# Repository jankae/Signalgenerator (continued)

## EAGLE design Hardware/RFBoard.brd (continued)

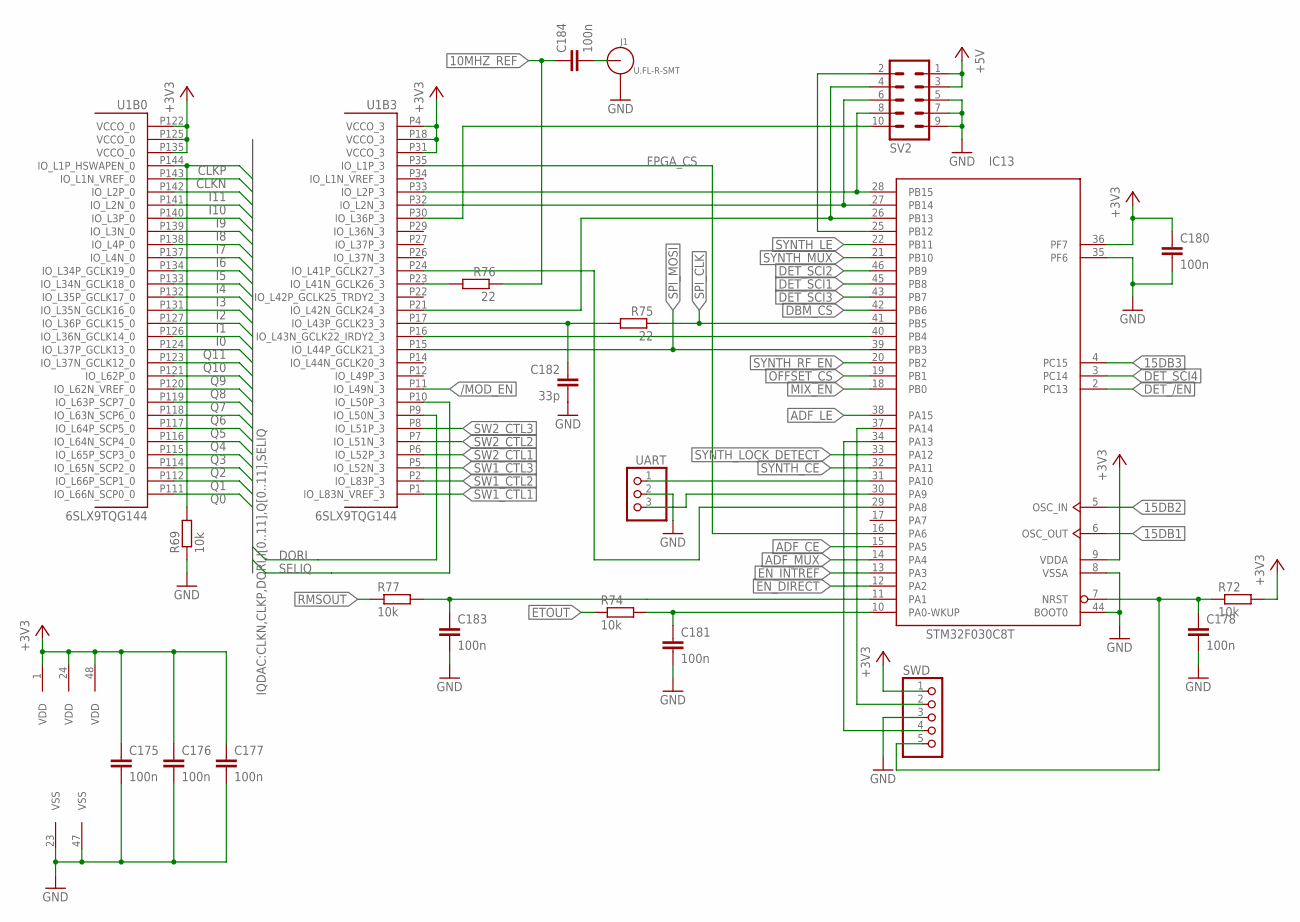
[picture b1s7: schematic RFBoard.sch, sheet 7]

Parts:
C175, C176, C177, C178, C180, C181, C183, C184: 100n; C0603
C182: 33p; C0603
IC13: STM32F030C8T; LQFP48
J1: U.FL-R-SMT; U.FL_SMT
R69, R72, R74, R77: 10k; R0603
R75, R76: 22; R0603
SV2: ML10
SWD: PINHD-1X5; 1X05
U1: 6SLX9TQG144; TQ144
UART: PINHD-1X3; 1X03

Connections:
10MHZ_REF: C184.1, R76.1; also elsewhere on the board
15DB1: IC13.6 (OSC_OUT); also elsewhere on the board
15DB2: IC13.5 (OSC_IN); also elsewhere on the board
15DB3: IC13.4 (PC15); also elsewhere on the board
+3V3: C175.1, C176.1, C177.1, C180.1, IC13.1 (VDD), IC13.9 (VDDA), IC13.24 (VDD), IC13.36 (PF7), IC13.48 (VDD), R72.2, SWD.1, U1.P4 (VCCO_3), U1.P18 (VCCO_3), U1.P31 (VCCO_3), U1.P122 (VCCO_0), U1.P125 (VCCO_0), U1.P135 (VCCO_0); also elsewhere on the board
+5V: SV2.1, SV2.3; also elsewhere on the board
/MOD_EN: U1.P11 (IO_L49N_3); also elsewhere on the board
ADF_CE: IC13.15 (PA5); also elsewhere on the board
ADF_LE: IC13.38 (PA15); also elsewhere on the board
ADF_MUX: IC13.14 (PA4); also elsewhere on the board
CLKN: U1.P143 (IO_L1N_VREF_0); also elsewhere on the board
CLKP: R69.2, U1.P144 (IO_L1P_HSWAPEN_0); also elsewhere on the board
CS: IC13.25 (PB12), SV2.2
CS_FPGA: SV2.10, U1.P30 (IO_L36P_3)
DBM_CS: IC13.42 (PB6); also elsewhere on the board
DET_/EN: IC13.2 (PC13); also elsewhere on the board
DET_SCI1: IC13.45 (PB8); also elsewhere on the board
DET_SCI2: IC13.46 (PB9); also elsewhere on the board
DET_SCI3: IC13.43 (PB7); also elsewhere on the board
DET_SCI4: IC13.3 (PC14); also elsewhere on the board
DORI: U1.P9 (IO_L50N_3); also elsewhere on the board
EN_DIRECT: IC13.12 (PA2); also elsewhere on the board
EN_INTREF: IC13.13 (PA3); also elsewhere on the board
ETOUT: R74.1; also elsewhere on the board
FPGA_CS: IC13.16 (PA6), U1.P35 (IO_L1P_3)
GND: C175.2, C176.2, C177.2, C178.2, C180.2, C181.2, C182.2, C183.2, IC13.8 (VSSA), IC13.23 (VSS), IC13.35 (PF6), IC13.44 (BOOT0), IC13.47 (VSS), J1.GND1, J1.GND2, R69.1, SV2.5, SV2.7, SV2.9, SWD.3, UART.2; also elsewhere on the board
I0: U1.P126 (IO_L36N_GCLK14_0); also elsewhere on the board
I1: U1.P127 (IO_L36P_GCLK15_0); also elsewhere on the board
I2: U1.P131 (IO_L35N_GCLK16_0); also elsewhere on the board
I3: U1.P132 (IO_L35P_GCLK17_0); also elsewhere on the board
I4: U1.P133 (IO_L34N_GCLK18_0); also elsewhere on the board
I5: U1.P134 (IO_L34P_GCLK19_0); also elsewhere on the board
I6: U1.P137 (IO_L4N_0); also elsewhere on the board
I7: U1.P138 (IO_L4P_0); also elsewhere on the board
I8: U1.P139 (IO_L3N_0); also elsewhere on the board
I9: U1.P140 (IO_L3P_0); also elsewhere on the board
I10: U1.P141 (IO_L2N_0); also elsewhere on the board
I11: U1.P142 (IO_L2P_0); also elsewhere on the board
MISO: IC13.27 (PB14), SV2.6, U1.P32 (IO_L2N_3)
MIX_EN: IC13.18 (PB0); also elsewhere on the board
MOSI: IC13.28 (PB15), SV2.8, U1.P33 (IO_L2P_3)
unnamed: C183.1, IC13.11 (PA1), R77.2
unnamed: C184.2, J1.SIG (ANT)
unnamed: IC13.29 (PA8), U1.P24 (IO_L41P_GCLK27_3)
unnamed: C181.1, IC13.10 (PA0-WKUP), R74.2
unnamed: C182.1, R75.2, U1.P17 (IO_L43P_GCLK23_3)
unnamed: IC13.40 (PB4), U1.P16 (IO_L43N_GCLK22_IRDY2_3)
unnamed: R76.2, U1.P23 (IO_L41N_GCLK26_3)
NRST: C178.1, IC13.7 (NRST), R72.1, SWD.5
OFFSET_CS: IC13.19 (PB1); also elsewhere on the board
Q0: U1.P111 (IO_L66N_SCP0_0); also elsewhere on the board
Q1: U1.P112 (IO_L66P_SCP1_0); also elsewhere on the board
Q2: U1.P114 (IO_L65N_SCP2_0); also elsewhere on the board
Q3: U1.P115 (IO_L65P_SCP3_0); also elsewhere on the board
Q4: U1.P116 (IO_L64N_SCP4_0); also elsewhere on the board
Q5: U1.P117 (IO_L64P_SCP5_0); also elsewhere on the board
Q6: U1.P118 (IO_L63N_SCP6_0); also elsewhere on the board
Q7: U1.P119 (IO_L63P_SCP7_0); also elsewhere on the board
Q8: U1.P120 (IO_L62N_VREF_0); also elsewhere on the board
Q9: U1.P121 (IO_L62P_0); also elsewhere on the board
Q10: U1.P123 (IO_L37N_GCLK12_0); also elsewhere on the board
Q11: U1.P124 (IO_L37P_GCLK13_0); also elsewhere on the board
RMSOUT: R77.1; also elsewhere on the board
RX: IC13.31 (PA10), UART.1
SCK: IC13.26 (PB13), SV2.4, U1.P21 (IO_L42N_GCLK24_3)
SELIQ: U1.P10 (IO_L50P_3); also elsewhere on the board
SPI_CLK: IC13.41 (PB5), R75.1; also elsewhere on the board
SPI_MOSI: IC13.39 (PB3), U1.P15 (IO_L44P_GCLK21_3); also elsewhere on the board
SW1_CTL1: U1.P1 (IO_L83N_VREF_3); also elsewhere on the board
SW1_CTL2: U1.P2 (IO_L83P_3); also elsewhere on the board
SW1_CTL3: U1.P5 (IO_L52N_3); also elsewhere on the board
SW2_CTL1: U1.P6 (IO_L52P_3); also elsewhere on the board
SW2_CTL2: U1.P7 (IO_L51N_3); also elsewhere on the board
SW2_CTL3: U1.P8 (IO_L51P_3); also elsewhere on the board
SWCLK: IC13.37 (PA14), SWD.2
SWDIO: IC13.34 (PA13), SWD.4
SYNTH_CE: IC13.32 (PA11); also elsewhere on the board
SYNTH_LE: IC13.22 (PB11); also elsewhere on the board
SYNTH_LOCK_DETECT: IC13.33 (PA12); also elsewhere on the board
SYNTH_MUX: IC13.21 (PB10); also elsewhere on the board
SYNTH_RF_EN: IC13.20 (PB2); also elsewhere on the board
TX: IC13.30 (PA9), UART.3

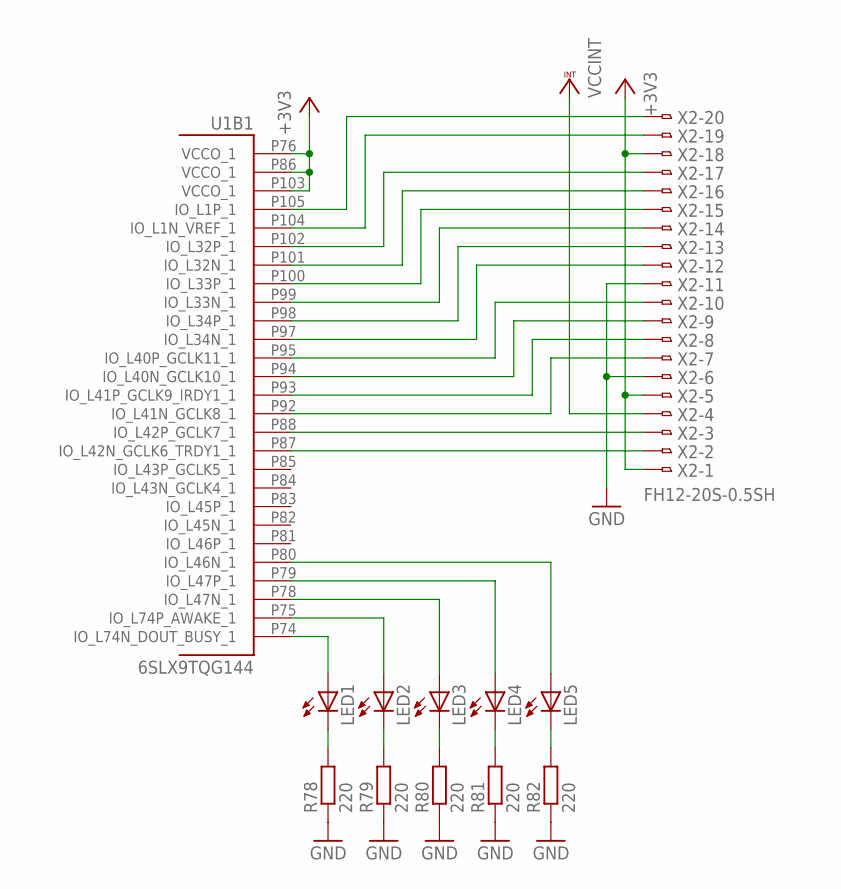
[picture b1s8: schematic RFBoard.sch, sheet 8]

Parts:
LED1, LED2, LED3, LED4, LED5: LEDCHIP-LED0603; CHIP-LED0603
R78, R79, R80, R81, R82: 220; R0603
U1: 6SLX9TQG144; TQ144
X2: FH12-20S-0.5SH

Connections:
+3V3: U1.P76 (VCCO_1), U1.P86 (VCCO_1), U1.P103 (VCCO_1), X2.1, X2.5, X2.18; also elsewhere on the board
GND: R78.1, R79.1, R80.1, R81.1, R82.1, X2.6, X2.11; also elsewhere on the board
unnamed: U1.P100 (IO_L33P_1), X2.15
unnamed: U1.P87 (IO_L42N_GCLK6_TRDY1_1), X2.2
unnamed: U1.P88 (IO_L42P_GCLK7_1), X2.3
unnamed: U1.P92 (IO_L41N_GCLK8_1), X2.7
unnamed: U1.P93 (IO_L41P_GCLK9_IRDY1_1), X2.8
unnamed: U1.P94 (IO_L40N_GCLK10_1), X2.9
unnamed: U1.P95 (IO_L40P_GCLK11_1), X2.10
unnamed: U1.P97 (IO_L34N_1), X2.12
unnamed: U1.P98 (IO_L34P_1), X2.13
unnamed: U1.P99 (IO_L33N_1), X2.14
unnamed: U1.P101 (IO_L32N_1), X2.16
unnamed: U1.P102 (IO_L32P_1), X2.17
unnamed: U1.P104 (IO_L1N_VREF_1), X2.19
unnamed: U1.P105 (IO_L1P_1), X2.20
unnamed: LED1.C, R78.2
unnamed: LED2.C, R79.2
unnamed: LED3.C, R80.2
unnamed: LED4.C, R81.2
unnamed: LED5.C, R82.2
unnamed: LED1.A, U1.P74 (IO_L74N_DOUT_BUSY_1)
unnamed: LED2.A, U1.P75 (IO_L74P_AWAKE_1)
unnamed: LED3.A, U1.P78 (IO_L47N_1)
unnamed: LED4.A, U1.P79 (IO_L47P_1)
unnamed: LED5.A, U1.P80 (IO_L46N_1)
VCCINT: X2.4; also elsewhere on the board

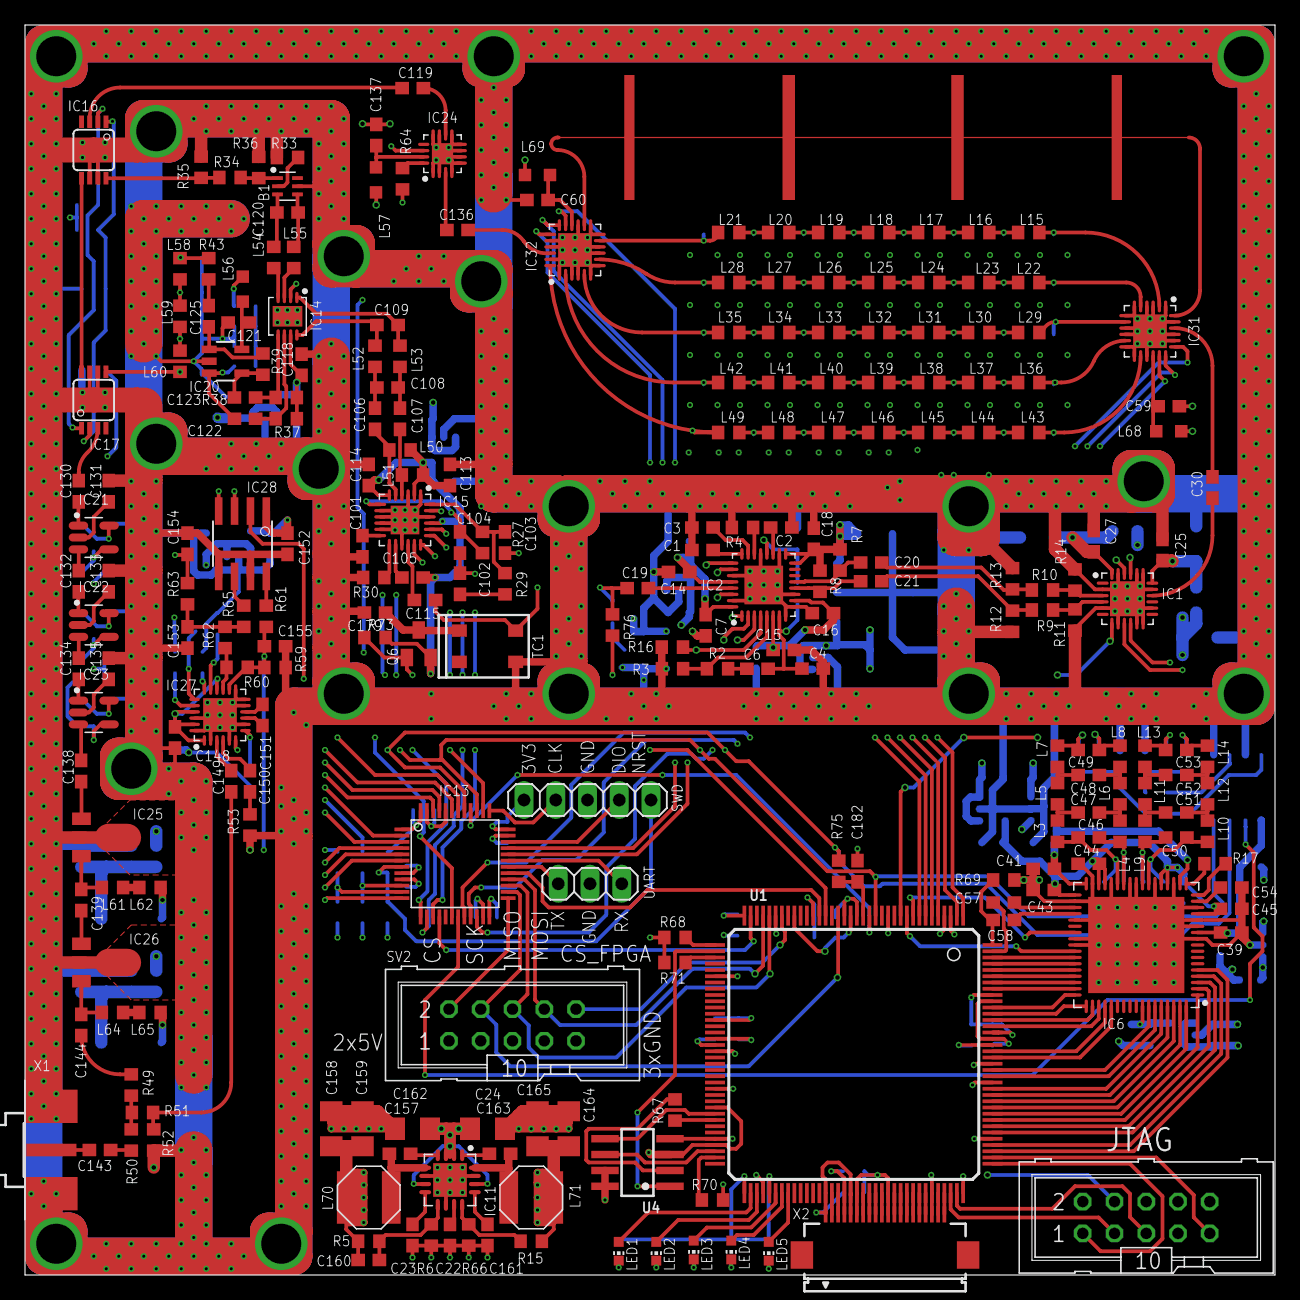
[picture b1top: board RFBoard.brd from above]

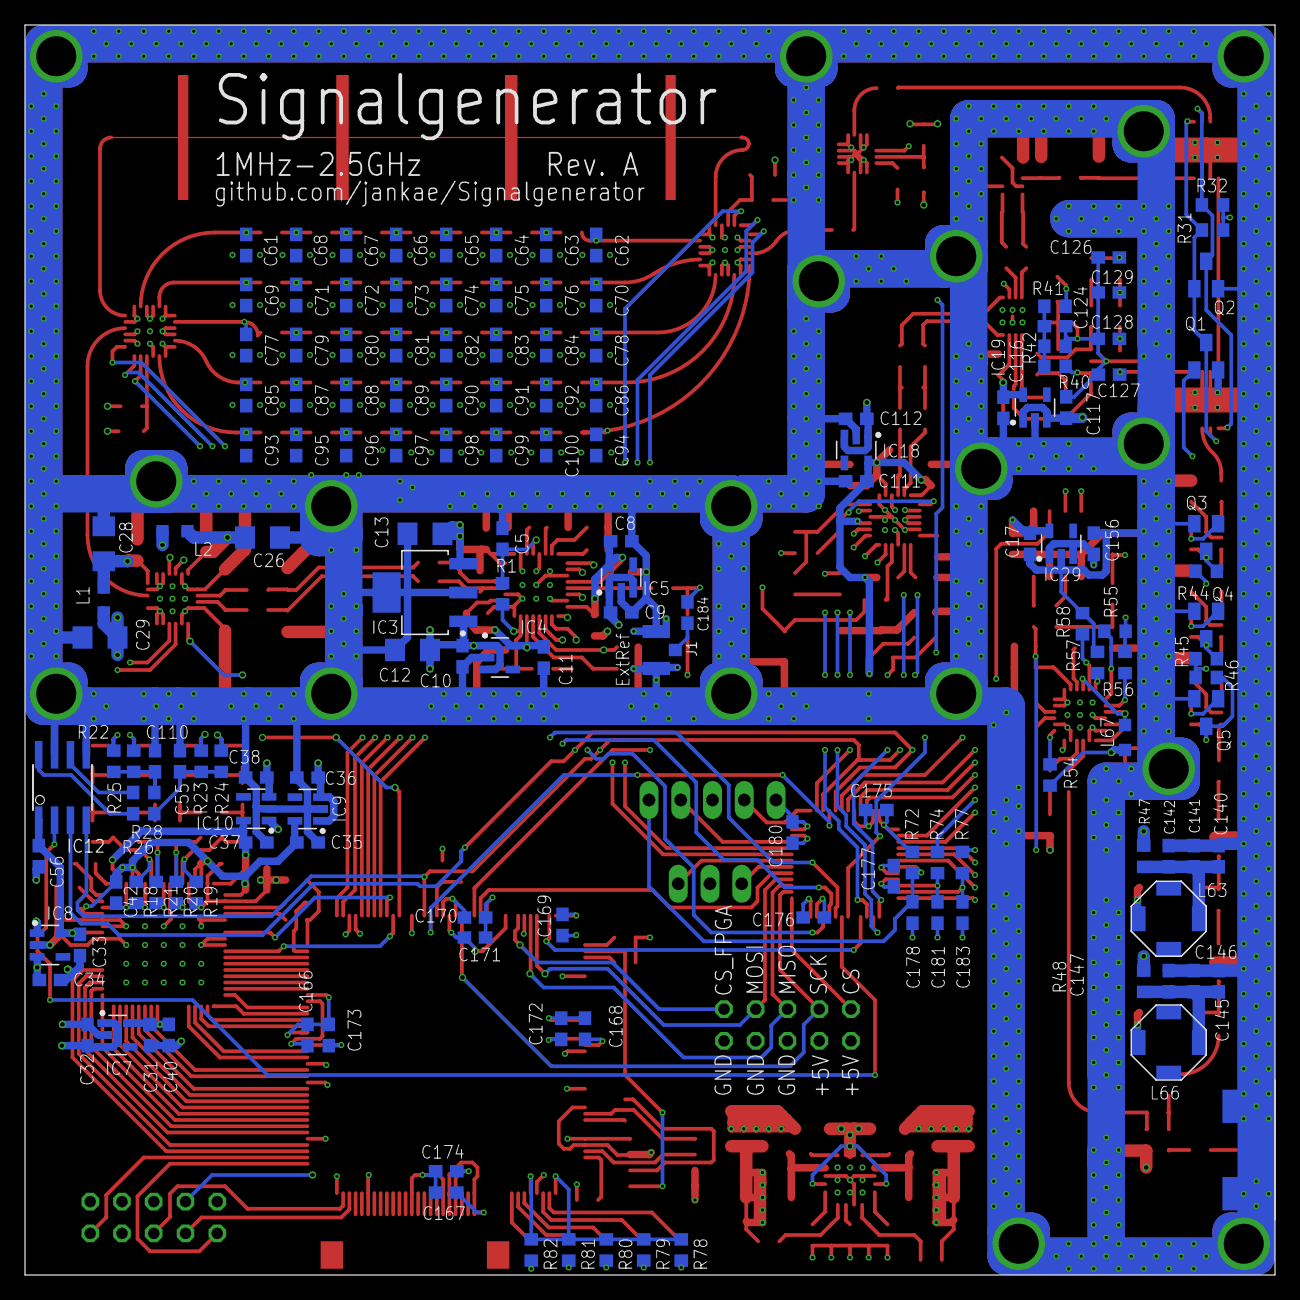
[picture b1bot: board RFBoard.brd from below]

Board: 4 copper layers, 100.0 x 100.0 mm, 390 parts (153 on the bottom side), 306 nets.

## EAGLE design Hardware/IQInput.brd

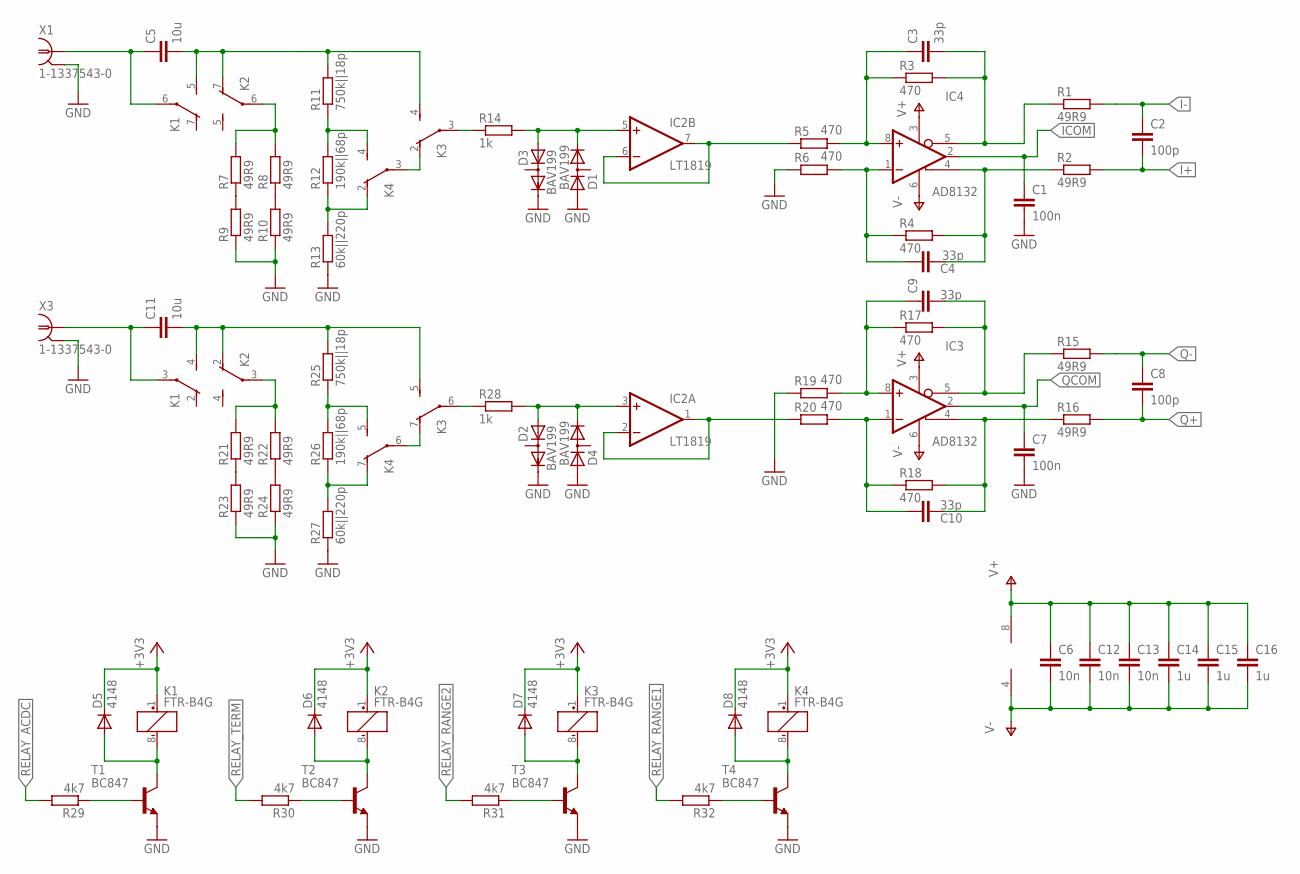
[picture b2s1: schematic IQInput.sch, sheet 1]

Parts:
C1, C7: 100n; C0603
C2, C8: 100p; C0603
C3, C4, C9, C10: 33p; C0603
C5, C11: 10u; C1206
C6, C12, C13: 10n; C0603
C14, C15, C16: 1u; C0603
D1, D2, D3, D4: BAV199; SOT23
D5, D6, D7, D8: 4148; MINIMELF
IC2: LT1819; SO08
IC3, IC4: AD8132; MSOP8
K1, K2, K3, K4: FTR-B4G
R1, R2, R15, R16: 49R9; R0603
R3, R4, R5, R6, R17, R18, R19, R20: 470; R0603
R7, R8, R9, R10, R21, R22, R23, R24: 49R9; R1206
R11, R25: 750k||18p; R0603
R12, R26: 190k||68p; R0603
R13, R27: 60k||220p; R0603
R14, R28: 1k; R0603
R29, R30, R31, R32: 4k7; R0603
T1, T2, T3, T4: BC847; SOT23
X1, X3: 1-1337543-0; AMP_227161

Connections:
+3V3: D5.C, D6.C, D7.C, D8.C, K1.1 (+), K2.1 (+), K3.1 (+), K4.1 (+); also elsewhere on the board
GND: C1.2, C7.2, D1.1 (A), D2.2 (C), D3.2 (C), D4.1 (A), R6.1, R9.1, R10.1, R13.1, R19.1, R23.1, R24.1, R27.1, T1.2 (E), T2.2 (E), T3.2 (E), T4.2 (E), X1.2, X3.2; also elsewhere on the board
I+: C2.2, R2.2; also elsewhere on the board
I-: C2.1, R1.2; also elsewhere on the board
ICOM: C1.1, IC4.2 (VOCM); also elsewhere on the board
unnamed: C4.2, IC4.4 (+OUT), R2.1, R4.2
unnamed: C5.1, K1.6, X1.1
unnamed: C4.1, IC4.1 (-IN), R4.1, R6.2
unnamed: C3.1, IC4.8 (+IN), R3.1, R5.2
unnamed: C3.2, IC4.5 (-OUT), R1.1, R3.2
unnamed: C5.2, K1.5 (S), K2.7 (O), K3.4 (S), R11.2
unnamed: R8.1, R10.2
unnamed: R7.1, R9.2
unnamed: K2.6, R7.2, R8.2
unnamed: K4.4 (S), R11.1, R12.2
unnamed: K4.2 (O), R12.1, R13.2
unnamed: K3.2 (O), K4.3
unnamed: K3.3, R14.1
unnamed: D1.2 (C), D3.1 (A), IC2.5 (+IN), R14.2
unnamed: IC2.6 (-IN), IC2.7 (OUT), R5.1
unnamed: C10.2, IC3.4 (+OUT), R16.1, R18.2
unnamed: C10.1, IC3.1 (-IN), R18.1, R20.2
unnamed: C9.1, IC3.8 (+IN), R17.1, R19.2
unnamed: C9.2, IC3.5 (-OUT), R15.1, R17.2
unnamed: C11.1, K1.3, X3.1
unnamed: C11.2, K1.4 (S), K2.2 (O), K3.5 (S), R25.2
unnamed: R22.1, R24.2
unnamed: R21.1, R23.2
unnamed: K2.3, R21.2, R22.2
unnamed: K4.5 (S), R25.1, R26.2
unnamed: K4.7 (O), R26.1, R27.2
unnamed: K3.7 (O), K4.6
unnamed: K3.6, R28.1
unnamed: D2.1 (A), D4.2 (C), IC2.3 (+IN), R28.2
unnamed: IC2.1 (OUT), IC2.2 (-IN), R20.1
unnamed: D5.A, K1.8 (-), T1.3 (C)
unnamed: R29.1, T1.1 (B)
unnamed: D6.A, K2.8 (-), T2.3 (C)
unnamed: R30.1, T2.1 (B)
unnamed: D7.A, K3.8 (-), T3.3 (C)
unnamed: R31.1, T3.1 (B)
unnamed: D8.A, K4.8 (-), T4.3 (C)
unnamed: R32.1, T4.1 (B)
Q+: C8.2, R16.2; also elsewhere on the board
Q-: C8.1, R15.2; also elsewhere on the board
QCOM: C7.1, IC3.2 (VOCM); also elsewhere on the board
RELAY_ACDC: R29.2; also elsewhere on the board
RELAY_RANGE1: R32.2; also elsewhere on the board
RELAY_RANGE2: R31.2; also elsewhere on the board
RELAY_TERM: R30.2; also elsewhere on the board
V+: C6.1, C12.1, C13.1, C14.1, C15.1, C16.1, IC2.8 (V+), IC3.3 (V+), IC4.3 (V+); also elsewhere on the board
V-: C6.2, C12.2, C13.2, C14.2, C15.2, C16.2, IC2.4 (V-), IC3.6 (V-), IC4.6 (V-); also elsewhere on the board

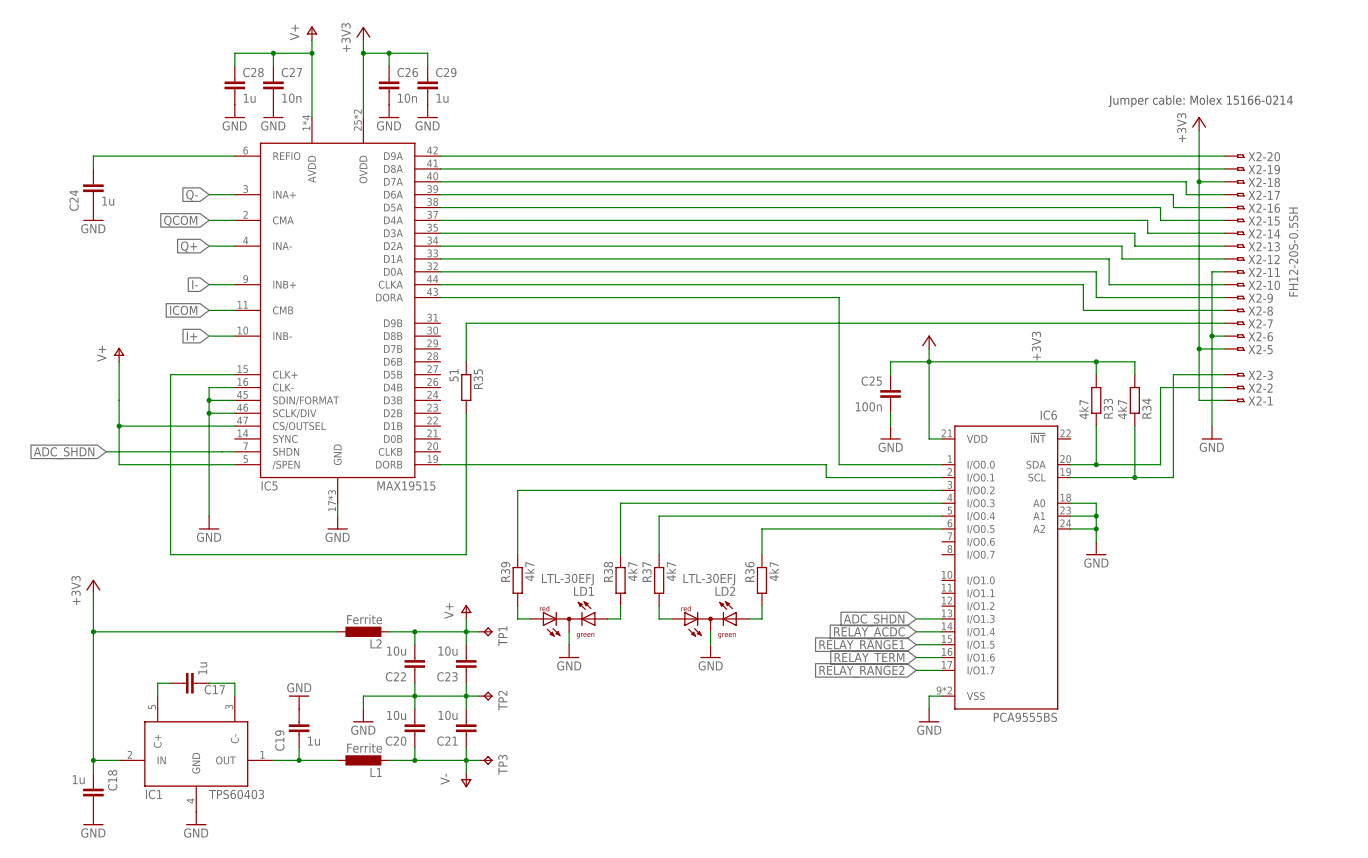
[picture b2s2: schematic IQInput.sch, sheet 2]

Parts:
C17, C18, C19, C24, C28, C29: 1u; C0603
C20, C21, C22, C23: 10u; C1206
C25: 100n; C0603
C26, C27: 10n; C0603
IC1: TPS60403; SOT23-5
IC5: MAX19515; QFN50P700X700X75-49T550N
IC6: PCA9555BS; HVQFN24
L1, L2: Ferrite; L2012C
LD1, LD2: LTL-30EFJ; DUOLED-C-5MM
R33, R34, R36, R37, R38, R39: 4k7; R0603
R35: 51; R0603
TP1, TP2, TP3: TPTP15R; TP15R
X2: FH12-20S-0.5SH

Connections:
+3V3: C18.2, C25.1, C26.1, C29.1, IC1.2 (IN), IC5.25 (OVDD), IC5.36 (OVDD), IC6.21 (VDD), L2.1, R33.2, R34.2, X2.1, X2.5, X2.18; also elsewhere on the board
ADC_SHDN: IC5.7 (SHDN), IC6.13 (I/O1.3)
GND: C18.1, C19.1, C20.2, C21.2, C22.1, C23.1, C24.2, C25.2, C26.2, C27.2, C28.2, C29.2, IC1.4 (GND), IC5.16 (CLK-), IC5.17 (GND), IC5.18 (GND), IC5.45 (SDIN/FORMAT), IC5.46 (SCLK/DIV), IC5.49 (GND), IC6.9 (VSS), IC6.18 (A0), IC6.23 (A1), IC6.24 (A2), IC6.TH (VSS), LD1.C, LD2.C, TP2.TP, X2.6, X2.11; also elsewhere on the board
I+: IC5.10 (INB-); also elsewhere on the board
I-: IC5.9 (INB+); also elsewhere on the board
ICOM: IC5.11 (CMB); also elsewhere on the board
unnamed: C17.1, IC1.5 (C+)
unnamed: C17.2, IC1.3 (C-)
unnamed: C19.2, IC1.1 (OUT), L1.1
unnamed: C24.1, IC5.6 (REFIO)
unnamed: IC5.43 (DORA), IC6.1 (I/O0.0)
unnamed: IC6.19 (SCL), R34.1, X2.3
unnamed: IC5.42 (D9A), X2.20
unnamed: IC5.41 (D8A), X2.19
unnamed: IC5.40 (D7A), X2.17
unnamed: IC5.39 (D6A), X2.16
unnamed: IC5.38 (D5A), X2.15
unnamed: IC5.37 (D4A), X2.14
unnamed: IC5.35 (D3A), X2.13
unnamed: IC5.34 (D2A), X2.12
unnamed: IC5.33 (D1A), X2.10
unnamed: IC5.32 (D0A), X2.9
unnamed: IC5.44 (CLKA), X2.8
unnamed: R35.1, X2.7
unnamed: IC5.15 (CLK+), R35.2
unnamed: IC6.20 (SDA), R33.1, X2.2
unnamed: IC5.19 (DORB), IC6.2 (I/O0.1)
unnamed: LD1.AR, R39.2
unnamed: LD1.AX (AG), R38.2
unnamed: LD2.AR, R37.2
unnamed: LD2.AX (AG), R36.2
unnamed: IC6.3 (I/O0.2), R39.1
unnamed: IC6.4 (I/O0.3), R38.1
unnamed: IC6.5 (I/O0.4), R37.1
unnamed: IC6.6 (I/O0.5), R36.1
Q+: IC5.4 (INA-); also elsewhere on the board
Q-: IC5.3 (INA+); also elsewhere on the board
QCOM: IC5.2 (CMA); also elsewhere on the board
RELAY_ACDC: IC6.14 (I/O1.4); also elsewhere on the board
RELAY_RANGE1: IC6.15 (I/O1.5); also elsewhere on the board
RELAY_RANGE2: IC6.17 (I/O1.7); also elsewhere on the board
RELAY_TERM: IC6.16 (I/O1.6); also elsewhere on the board
V+: C22.2, C23.2, C27.1, C28.1, IC5.1 (AVDD), IC5.5 (/SPEN), IC5.12 (AVDD), IC5.13 (AVDD), IC5.47 (CS/OUTSEL), IC5.48 (AVDD), L2.2, TP1.TP; also elsewhere on the board
V-: C20.1, C21.1, L1.2, TP3.TP; also elsewhere on the board

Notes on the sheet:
Jumper cable: Molex 15166-0214

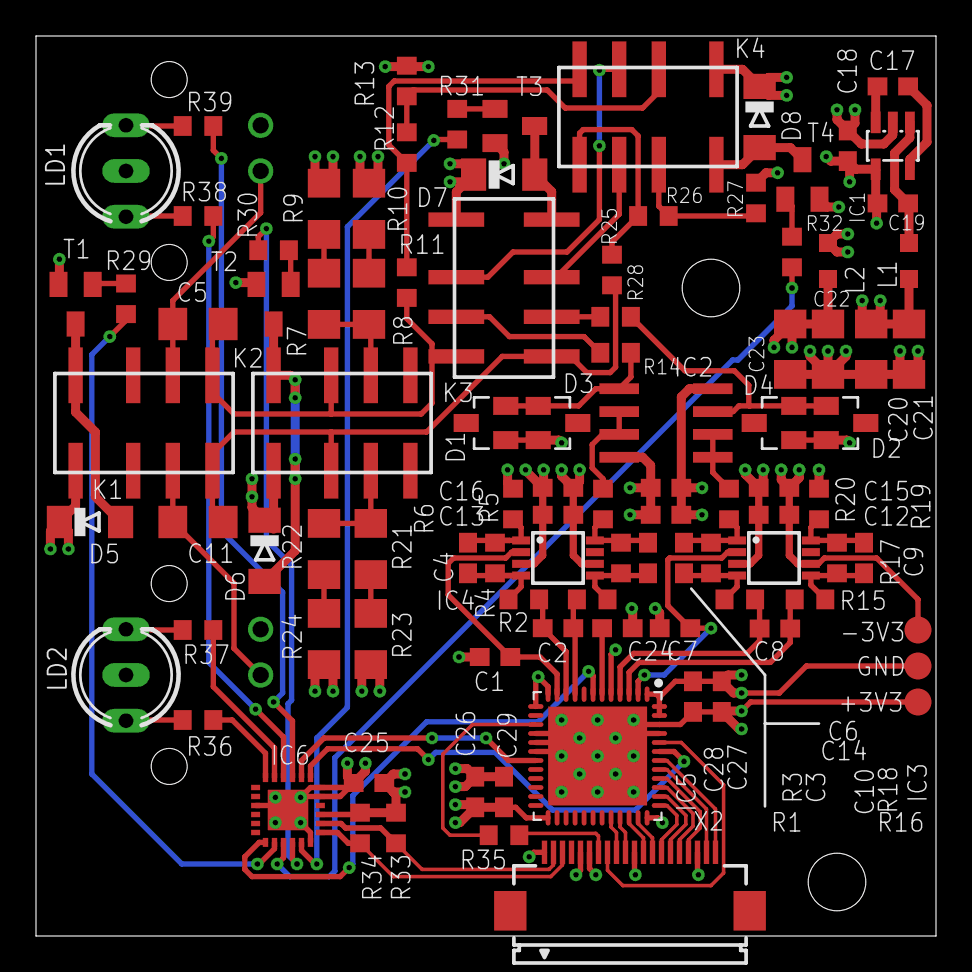
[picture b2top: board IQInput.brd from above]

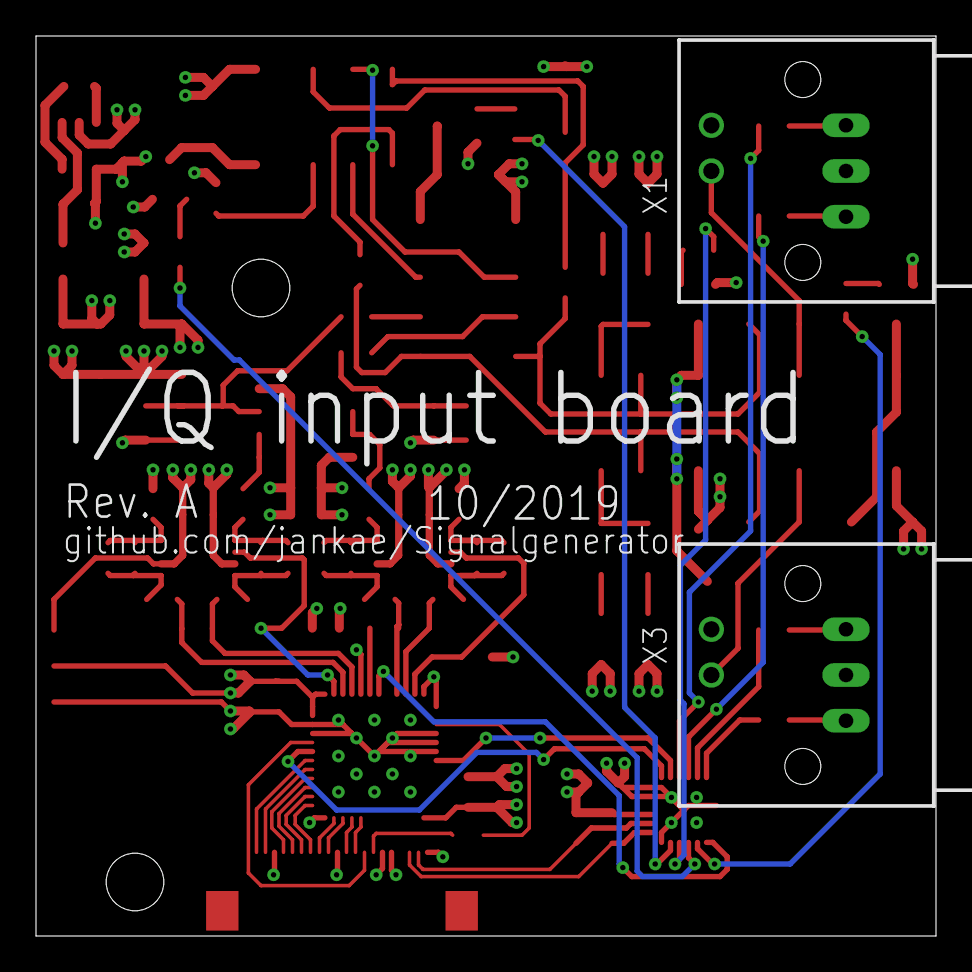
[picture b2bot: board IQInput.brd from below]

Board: 4 copper layers, 50.0 x 50.0 mm, 100 parts (2 on the bottom side), 82 nets.

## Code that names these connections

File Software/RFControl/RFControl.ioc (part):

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Mcu.Name=STM32F030C8Tx
Mcu.Package=LQFP48
Mcu.UserName=STM32F030C8Tx
PA1.Mode=IN1
PA1.Signal=ADC_IN1
PA10.Mode=Asynchronous
PA10.Signal=USART1_RX
PA11.GPIOParameters=GPIO_Label
PA11.GPIO_Label=SYNTH_CE
PA11.Signal=GPIO_Output
PA12.GPIOParameters=GPIO_PuPd,GPIO_Label
PA12.GPIO_Label=SYNTH_LD
PA12.GPIO_PuPd=GPIO_PULLUP
PA12.Signal=GPIO_Input
PA13.Mode=Serial_Wire
PA13.Signal=SYS_SWDIO
PA14.Mode=Serial_Wire
PA14.Signal=SYS_SWCLK
PA15.GPIOParameters=GPIO_Label
PA15.GPIO_Label=ADF_LE
PA15.Signal=GPIO_Output
PA2.GPIOParameters=PinState,GPIO_Label
PA2.GPIO_Label=EN_DIRECT
PA2.PinState=GPIO_PIN_SET
PA2.Signal=GPIO_Output
PA3.GPIOParameters=PinState,GPIO_Label
PA3.GPIO_Label=EN_INTREF
PA3.PinState=GPIO_PIN_SET
PA3.Signal=GPIO_Output
PA4.GPIOParameters=GPIO_PuPd,GPIO_Label
PA4.GPIO_Label=ADF_MUX
PA4.GPIO_PuPd=GPIO_PULLUP
PA4.Signal=GPIO_Input
PA5.GPIOParameters=GPIO_Label
PA5.GPIO_Label=ADF_CE
PA5.Signal=GPIO_Output
PA6.GPIOParameters=PinState,GPIO_Label
PA6.GPIO_Label=FPGA_CS
PA6.PinState=GPIO_PIN_SET
PA6.Signal=GPIO_Output
PA8.GPIOParameters=GPIO_Label
PA8.GPIO_Label=FPGA_RESET
PA8.Signal=GPIO_Output
PA9.Mode=Asynchronous
PA9.Signal=USART1_TX
PB0.GPIOParameters=GPIO_Label
PB0.GPIO_Label=MIX_EN
PB0.Signal=GPIO_Output
PB1.GPIOParameters=PinState,GPIO_Label
PB1.GPIO_Label=OFFSET_CS
PB1.PinState=GPIO_PIN_SET
PB1.Signal=GPIO_Output
PB10.GPIOParameters=GPIO_Label
PB10.GPIO_Label=SYNTH_MUX
PB10.Signal=GPIO_Input
PB11.GPIOParameters=GPIO_Label
PB11.GPIO_Label=SYNTH_LE
PB11.Signal=GPIO_Output
PB12.Mode=NSS_Signal_Hard_Input
PB12.Signal=SPI2_NSS
PB13.Mode=Full_Duplex_Slave
PB13.Signal=SPI2_SCK
PB14.Mode=Full_Duplex_Slave
PB14.Signal=SPI2_MISO
PB15.Mode=Full_Duplex_Slave
PB15.Signal=SPI2_MOSI
PB2.GPIOParameters=GPIO_Label
PB2.GPIO_Label=SYNTH_RF_EN
PB2.Signal=GPIO_Output
PB3.Mode=Full_Duplex_Master
PB3.Signal=SPI1_SCK
PB4.Mode=Full_Duplex_Master
PB4.Signal=SPI1_MISO
PB5.Mode=Full_Duplex_Master
PB5.Signal=SPI1_MOSI
PB6.GPIOParameters=PinState,GPIO_Label
PB6.GPIO_Label=DBM_CS
PB6.PinState=GPIO_PIN_SET
PB6.Signal=GPIO_Output
PB7.GPIOParameters=GPIO_Label
PB7.GPIO_Label=DET_SCI3
PB7.Signal=GPIO_Output
PB8.GPIOParameters=GPIO_Label
PB8.GPIO_Label=DET_SCI1
PB8.Signal=GPIO_Output
PB9.GPIOParameters=GPIO_Label
PB9.GPIO_Label=DET_SCI2
PB9.Signal=GPIO_Output
PC13.GPIOParameters=PinState,GPIO_Label
PC13.GPIO_Label=DET_EN
PC13.PinState=GPIO_PIN_SET
PC13.Signal=GPIO_Output
PC14-OSC32_IN.GPIOParameters=GPIO_Label
PC14-OSC32_IN.GPIO_Label=DET_SCI4
PC14-OSC32_IN.Signal=GPIO_Output
PC15-OSC32_OUT.GPIOParameters=PinState,GPIO_Label
PC15-OSC32_OUT.GPIO_Label=DB15_3
PC15-OSC32_OUT.PinState=GPIO_PIN_SET
PC15-OSC32_OUT.Signal=GPIO_Output
PF0-OSC_IN.GPIOParameters=PinState,GPIO_Label
PF0-OSC_IN.GPIO_Label=DB15_2
PF0-OSC_IN.PinState=GPIO_PIN_SET
PF0-OSC_IN.Signal=GPIO_Output
PF1-OSC_OUT.GPIOParameters=PinState,GPIO_Label
PF1-OSC_OUT.GPIO_Label=DB15_1
PF1-OSC_OUT.PinState=GPIO_PIN_SET
PF1-OSC_OUT.Signal=GPIO_Output
RCC.SYSCLKFreq_VALUE=48000000
RCC.SYSCLKSource=RCC_SYSCLKSOURCE_PLLCLK
board=RFControl

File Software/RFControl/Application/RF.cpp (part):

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#include "main.h"
extern SPI_HandleTypeDef hspi1;

static MCP48X2 PowerDAC = MCP48X2(&hspi1, DBM_CS_GPIO_Port, DBM_CS_Pin);
static ADF4360 HeterodyneLO = ADF4360(&hspi1, ADF_CE_GPIO_Port, ADF_CE_Pin,
		ADF_LE_GPIO_Port, ADF_LE_Pin, ADF_MUX_GPIO_Port, ADF_MUX_Pin);
static MAX2871 Synthesizer = MAX2871(&hspi1, SYNTH_CE_GPIO_Port, SYNTH_CE_Pin,
		SYNTH_LE_GPIO_Port, SYNTH_LE_Pin, SYNTH_MUX_GPIO_Port, SYNTH_MUX_Pin,
		SYNTH_RF_EN_GPIO_Port, SYNTH_RF_EN_Pin, SYNTH_LD_GPIO_Port,
SYNTH_LD_Pin);

extern ADC_HandleTypeDef hadc;
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		HeterodyneLO.SetFrequency(1000000000);
		HeterodyneLO.Update();
		// enable mixer
		MIX_EN_GPIO_Port->BSRR = MIX_EN_Pin;
		// set switches to heterodyne path
		EN_DIRECT_GPIO_Port->BSRR = EN_DIRECT_Pin << 16;
		LOG(Log_RF, LevelDebug, "Heterodyne path enabled");
		spi_status->Status.HeterodynePLLON = 1;
	} else {
		// disable PLL
		HeterodyneLO.ChipEnable(false);
		// disable mixer
		MIX_EN_GPIO_Port->BSRR = MIX_EN_Pin << 16;
		// set switches to direct path
		EN_DIRECT_GPIO_Port->BSRR = EN_DIRECT_Pin;
		LOG(Log_RF, LevelDebug, "Heterodyne path disabled");
		spi_status->Status.HeterodynePLLON = 0;
	}
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	using namespace FPGA;
	switch(l) {
	case LPF::LP340M:
		SetGPIO(GPIO::SW1_CTL1 | GPIO::SW1_CTL3 | GPIO::SW2_CTL2);
		ResetGPIO(GPIO::SW1_CTL2 | GPIO::SW2_CTL1 | GPIO::SW2_CTL3);
		LOG(Log_RF, LevelDebug, "Selected 340MHz filter");
		break;
	case LPF::LP500M:
		SetGPIO(GPIO::SW1_CTL3 | GPIO::SW2_CTL1 | GPIO::SW2_CTL2);
		ResetGPIO(GPIO::SW1_CTL1 | GPIO::SW1_CTL2 | GPIO::SW2_CTL3);
		LOG(Log_RF, LevelDebug, "Selected 500MHz filter");
		break;
	case LPF::LP750M:
		SetGPIO(GPIO::SW1_CTL1 | GPIO::SW1_CTL2 | GPIO::SW2_CTL3);
		ResetGPIO(GPIO::SW1_CTL3 | GPIO::SW2_CTL1 | GPIO::SW2_CTL2);
		LOG(Log_RF, LevelDebug, "Selected 750MHz filter");
		break;
	case LPF::LP1G1:
		SetGPIO(GPIO::SW1_CTL2 | GPIO::SW2_CTL1 | GPIO::SW2_CTL3);
		ResetGPIO(GPIO::SW1_CTL1 | GPIO::SW1_CTL3 | GPIO::SW2_CTL2);
		LOG(Log_RF, LevelDebug, "Selected 1.1GHz filter");
		break;
	case LPF::LP1G7:
		SetGPIO(GPIO::SW1_CTL1 | GPIO::SW2_CTL1 | GPIO::SW2_CTL2 | GPIO::SW2_CTL3);
		ResetGPIO(GPIO::SW1_CTL2 | GPIO::SW1_CTL3);
		LOG(Log_RF, LevelDebug, "Selected 1.7GHz filter");
		break;
	case LPF::LP2G5:
		SetGPIO(GPIO::SW1_CTL1 | GPIO::SW1_CTL2 | GPIO::SW1_CTL3 | GPIO::SW2_CTL1);
		ResetGPIO(GPIO::SW2_CTL2 | GPIO::SW2_CTL3);
		LOG(Log_RF, LevelDebug, "Selected 2.5GHz filter");
		break;
	}
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
void RF::InternalReference(bool enabled) {
	if (enabled) {
		EN_INTREF_GPIO_Port->BSRR = EN_INTREF_Pin << 16;
		if (spi_status) {
			spi_status->Status.IntRefON = 1;
		}
	} else {
		EN_INTREF_GPIO_Port->BSRR = EN_INTREF_Pin;
		if (spi_status) {
			spi_status->Status.IntRefON = 0;
		}
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
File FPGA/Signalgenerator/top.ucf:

CONFIG VCCAUX=3.3;
NET "CLK" LOC = P23;
NET "CLK" PERIOD = 100ns;


NET "CLK" IOSTANDARD = LVCMOS33;
NET "RESET" IOSTANDARD = LVCMOS33;
NET "SPI_EXT_CS" IOSTANDARD = LVCMOS33;
NET "SPI_EXT_MOSI" IOSTANDARD = LVCMOS33;
NET "SPI_EXT_SCK" IOSTANDARD = LVCMOS33;
NET "SPI_INT_CS" IOSTANDARD = LVCMOS33;
NET "SPI_INT_MOSI" IOSTANDARD = LVCMOS33;
NET "SPI_INT_SCK" IOSTANDARD = LVCMOS33;
NET "MOD_EN" IOSTANDARD = LVCMOS33;
NET "SPI_EXT_MISO" IOSTANDARD = LVCMOS33;
NET "SELIQ" IOSTANDARD = LVCMOS33;
NET "DORI" IOSTANDARD = LVCMOS33;
NET "SPI_INT_MISO" IOSTANDARD = LVCMOS33;
NET "I[11]" IOSTANDARD = LVCMOS33;
NET "I[10]" IOSTANDARD = LVCMOS33;
NET "I[9]" IOSTANDARD = LVCMOS33;
NET "I[8]" IOSTANDARD = LVCMOS33;
NET "I[7]" IOSTANDARD = LVCMOS33;
NET "I[6]" IOSTANDARD = LVCMOS33;
NET "I[5]" IOSTANDARD = LVCMOS33;
NET "I[4]" IOSTANDARD = LVCMOS33;
NET "I[3]" IOSTANDARD = LVCMOS33;
NET "I[2]" IOSTANDARD = LVCMOS33;
NET "I[1]" IOSTANDARD = LVCMOS33;
NET "I[0]" IOSTANDARD = LVCMOS33;
NET "Q[11]" IOSTANDARD = LVCMOS33;
NET "Q[10]" IOSTANDARD = LVCMOS33;
NET "Q[9]" IOSTANDARD = LVCMOS33;
NET "Q[8]" IOSTANDARD = LVCMOS33;
NET "Q[7]" IOSTANDARD = LVCMOS33;
NET "Q[6]" IOSTANDARD = LVCMOS33;
NET "Q[5]" IOSTANDARD = LVCMOS33;
NET "Q[4]" IOSTANDARD = LVCMOS33;
NET "Q[3]" IOSTANDARD = LVCMOS33;
NET "Q[2]" IOSTANDARD = LVCMOS33;
NET "Q[1]" IOSTANDARD = LVCMOS33;
NET "Q[0]" IOSTANDARD = LVCMOS33;
NET "SW2_CTL[2]" IOSTANDARD = LVCMOS33;
NET "SW2_CTL[1]" IOSTANDARD = LVCMOS33;
NET "SW2_CTL[0]" IOSTANDARD = LVCMOS33;
NET "SW1_CTL[2]" IOSTANDARD = LVCMOS33;
NET "SW1_CTL[1]" IOSTANDARD = LVCMOS33;
NET "SW1_CTL[0]" IOSTANDARD = LVCMOS33;
NET "LED[4]" IOSTANDARD = LVCMOS33;
NET "LED[3]" IOSTANDARD = LVCMOS33;
NET "LED[2]" IOSTANDARD = LVCMOS33;
NET "LED[1]" IOSTANDARD = LVCMOS33;
NET "LED[0]" IOSTANDARD = LVCMOS33;

NET "ADC_SAMPLE_CLK" IOSTANDARD = LVCMOS33;
NET "ADC_DCLK" IOSTANDARD = LVCMOS33;
NET "ADC_DATA[0]" IOSTANDARD = LVCMOS33;
NET "ADC_DATA[1]" IOSTANDARD = LVCMOS33;
NET "ADC_DATA[2]" IOSTANDARD = LVCMOS33;
NET "ADC_DATA[3]" IOSTANDARD = LVCMOS33;
NET "ADC_DATA[4]" IOSTANDARD = LVCMOS33;
NET "ADC_DATA[5]" IOSTANDARD = LVCMOS33;
NET "ADC_DATA[6]" IOSTANDARD = LVCMOS33;
NET "ADC_DATA[7]" IOSTANDARD = LVCMOS33;
NET "ADC_DATA[8]" IOSTANDARD = LVCMOS33;
NET "ADC_DATA[9]" IOSTANDARD = LVCMOS33;

NET "SDA" IOSTANDARD = LVCMOS33;
NET "SCL" IOSTANDARD = LVCMOS33;

NET "RESET" LOC = P24;
NET "SPI_EXT_CS" LOC = P30;
NET "SPI_EXT_MOSI" LOC = P33;
NET "SPI_EXT_SCK" LOC = P21;
NET "SPI_INT_CS" LOC = P35;
NET "SPI_INT_MOSI" LOC = P15;
NET "SPI_INT_SCK" LOC = P17;

NET "MOD_EN" LOC = P11;
NET "SELIQ" LOC = P10;
NET "SPI_EXT_MISO" LOC = P32;
NET "SPI_INT_MISO" LOC = P16;
NET "I[11]" LOC = P142;
NET "I[10]" LOC = P141;
NET "I[9]" LOC = P140;
NET "I[8]" LOC = P139;
NET "I[7]" LOC = P138;
NET "I[6]" LOC = P137;
NET "I[5]" LOC = P134;
NET "I[4]" LOC = P133;
NET "I[3]" LOC = P132;
NET "I[2]" LOC = P131;
NET "I[1]" LOC = P127;
NET "I[0]" LOC = P126;
NET "Q[11]" LOC = P124;
NET "Q[9]" LOC = P121;
NET "Q[7]" LOC = P119;
NET "Q[8]" LOC = P120;
NET "Q[6]" LOC = P118;
NET "Q[5]" LOC = P117;
NET "Q[4]" LOC = P116;
NET "Q[3]" LOC = P115;
NET "Q[2]" LOC = P114;
NET "Q[1]" LOC = P112;
NET "Q[0]" LOC = P111;
NET "SW1_CTL[0]" LOC = P1;
NET "SW1_CTL[1]" LOC = P2;
NET "SW1_CTL[2]" LOC = P5;
NET "SW2_CTL[2]" LOC = P8;
NET "SW2_CTL[0]" LOC = P6;
NET "SW2_CTL[1]" LOC = P7;
NET "LED[4]" LOC = P80;
NET "LED[3]" LOC = P79;
NET "LED[2]" LOC = P78;
NET "LED[1]" LOC = P75;
NET "LED[0]" LOC = P74;
NET "Q[10]" LOC = P123;
NET "DORI" LOC = P9;

NET "ADC_SAMPLE_CLK" LOC = P92;
NET "ADC_DCLK" LOC = P93;
NET "ADC_DATA[0]" LOC = P94;
NET "ADC_DATA[1]" LOC = P95;
NET "ADC_DATA[2]" LOC = P97;
NET "ADC_DATA[3]" LOC = P98;
NET "ADC_DATA[4]" LOC = P99;
NET "ADC_DATA[5]" LOC = P100;
NET "ADC_DATA[6]" LOC = P101;
NET "ADC_DATA[7]" LOC = P102;
NET "ADC_DATA[8]" LOC = P104;
NET "ADC_DATA[9]" LOC = P105;

NET "SDA" LOC = P87;
NET "SCL" LOC = P88;

# PlanAhead Generated physical constraints 

NET "CLK_DAC_N" LOC = P143;
NET "CLK_DAC_P" LOC = P144;

# PlanAhead Generated IO constraints 

NET "CLK_DAC_N" IOSTANDARD = DIFF_SSTL3_II;
NET "CLK_DAC_P" IOSTANDARD = DIFF_SSTL3_II;

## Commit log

2019-05-28 Partial schematic
2019-05-30 Heterodyne path sheet
2019-06-01 RF part of schematic finished, placed most components on PCB
2019-06-01 Almost all RF routing
2019-06-02 FPGA + power supply added
2019-06-02 MCU added
2019-06-03 Routing of schematic completed
2019-06-04 Via stitching, missing connections, FPGA pins to FFC connector
2019-06-05 Silkscreen, MOD_EN wire
2019-06-05 PCB finished
2019-06-08 MAX2871/ADF4360 drivers
2019-06-09 MCP48X2 driver, RF path logic
2019-06-10 GUI copy and adjustments for menu from battery-sim
2019-06-10 Submenus working
2019-06-12 Remove application code from battery-sim, added item chooser as menu entry
2019-06-25 Hardfault handler output, button input bugfixing, menuvalue with input dialog
2019-06-26 bugfixes, MenuAction, main screen layout
2019-06-29 untested implementation of SPI protocol between frontpanel and RF board
2019-06-29 Switched to correct MCU version, bugfixes in PLL drivers
2019-06-29 --amend
2019-06-29 PLL loop filter values changed
2019-06-30 Bugfixes
2019-07-01 Bugfixes heterodyne path
2019-07-01 Value changes amplitude control feedback loop
2019-07-05 Bugfix: Lockissue + basic FM modulation
2019-07-13 Calibration of amplitude + persistent storage in last FLASH page
2019-07-13 Modulation source: PRBS added + preparations for streaming
2019-07-13 VHDL files
2019-07-13 Pictures/block diagram of RF board
2019-07-13 Ignore 3D CAD file
2019-07-14 Reset streaming FIFO when unused
2019-07-14 Implementation of streaming modulation from frontpanel to FPGA
2019-07-23 USB audio experiments + added (almost useless) balance calibration
2019-08-27 Added digital amplitude control
2019-09-12 Template for certain GUI elements, allowing frequencies above 2.1GHz
2019-09-12 Enabling modulation after output amplitude has settled
2019-09-14 Bugfixes: Entry constructor + FM modulation level correction
2019-09-15 patial GUI implementation of QAM modulation
2019-09-16 I/Q functionality added to modulator
2019-09-18 Basic working QAM modulation
2019-10-08 Pictures of RF shield
2019-10-08 Screenshots of produced signal
2019-10-08 Scaling values for constellation diagram
2019-10-08 unsaved ISE work
2019-10-10 SevenSegment changeable with arrow keys/encoder
2019-10-10 Eclipse update
2019-10-11 Schematic + Routing of IQ input board
2019-10-11 Stepfile for display adapter
2019-10-11 Silkscreen
2019-10-12 FIR filter tests with multiplexed multipliers
2019-10-12 Added pulse shaping to QAM modulation (timing constraints not met yet)
2019-10-13 Basic pulse shaping working (no GUI configuration yet)
2019-10-13 Bugfix: samples per symbol off by one
2019-10-14 Reworked menu structure for modulation settings
2019-10-14 Limits for menu entries
2019-10-15 FPGA speed doubled, FIR taps increased
2019-10-16 Added value to input protection resistor
2019-10-16 Specified values
2019-10-17 Made room for on/off switch
2019-10-17 Capsulated FPGA access, buttons for RF/modulation on/off
2019-10-18 RF documentation
2019-10-19 Tex drawing of modulation generation in FPGA
2019-10-20 Added testpoints, changes to silkscreen, created Gerber
2019-10-21 Switched to 10MHz ref clk as FPGA clk, added reset, ADC sampling for external I/Q input
2019-10-21 CubeMX update, added FPGA reset
2019-10-21 Check communication with RF board at startup
2019-10-21 Menu stubs for external modulation
2019-10-22 Untested implementation of external modulation + removed warnings
2019-10-22 Passing external modulation signals through gluelogic
2019-10-28 External modulation added to SPI protocol on master side
2019-11-03 Output level control while modulation is active
2019-11-03 Slight improvements to balance calibration
2019-11-03 Added reset to PLL
2019-11-09 Bugfixes: external modulation + I2C master in FPGA
2019-11-11 Fixed external modulation input, balance calibration. Preparations for skew calibration
2019-11-11 Part values corrected
2019-11-11 Simulation of IQ input and DDS section
2019-11-11 Fix scaling of DAC from FIR
2019-11-11 External modulation lowpass + bugfix constellation scaling
2019-11-11 IQ input board startup check and overload reporting
2019-11-16 Improved calibration routines
2019-11-18 Frontpanel adjustments
2019-11-18 Pictures of assembled device
2019-11-18 BOM IQ input board
2020-03-21 External modulation input usable as modulation source
2020-03-22 Bugfixes: FPGA I2C SDA glitch, negative offsets for external modulation
